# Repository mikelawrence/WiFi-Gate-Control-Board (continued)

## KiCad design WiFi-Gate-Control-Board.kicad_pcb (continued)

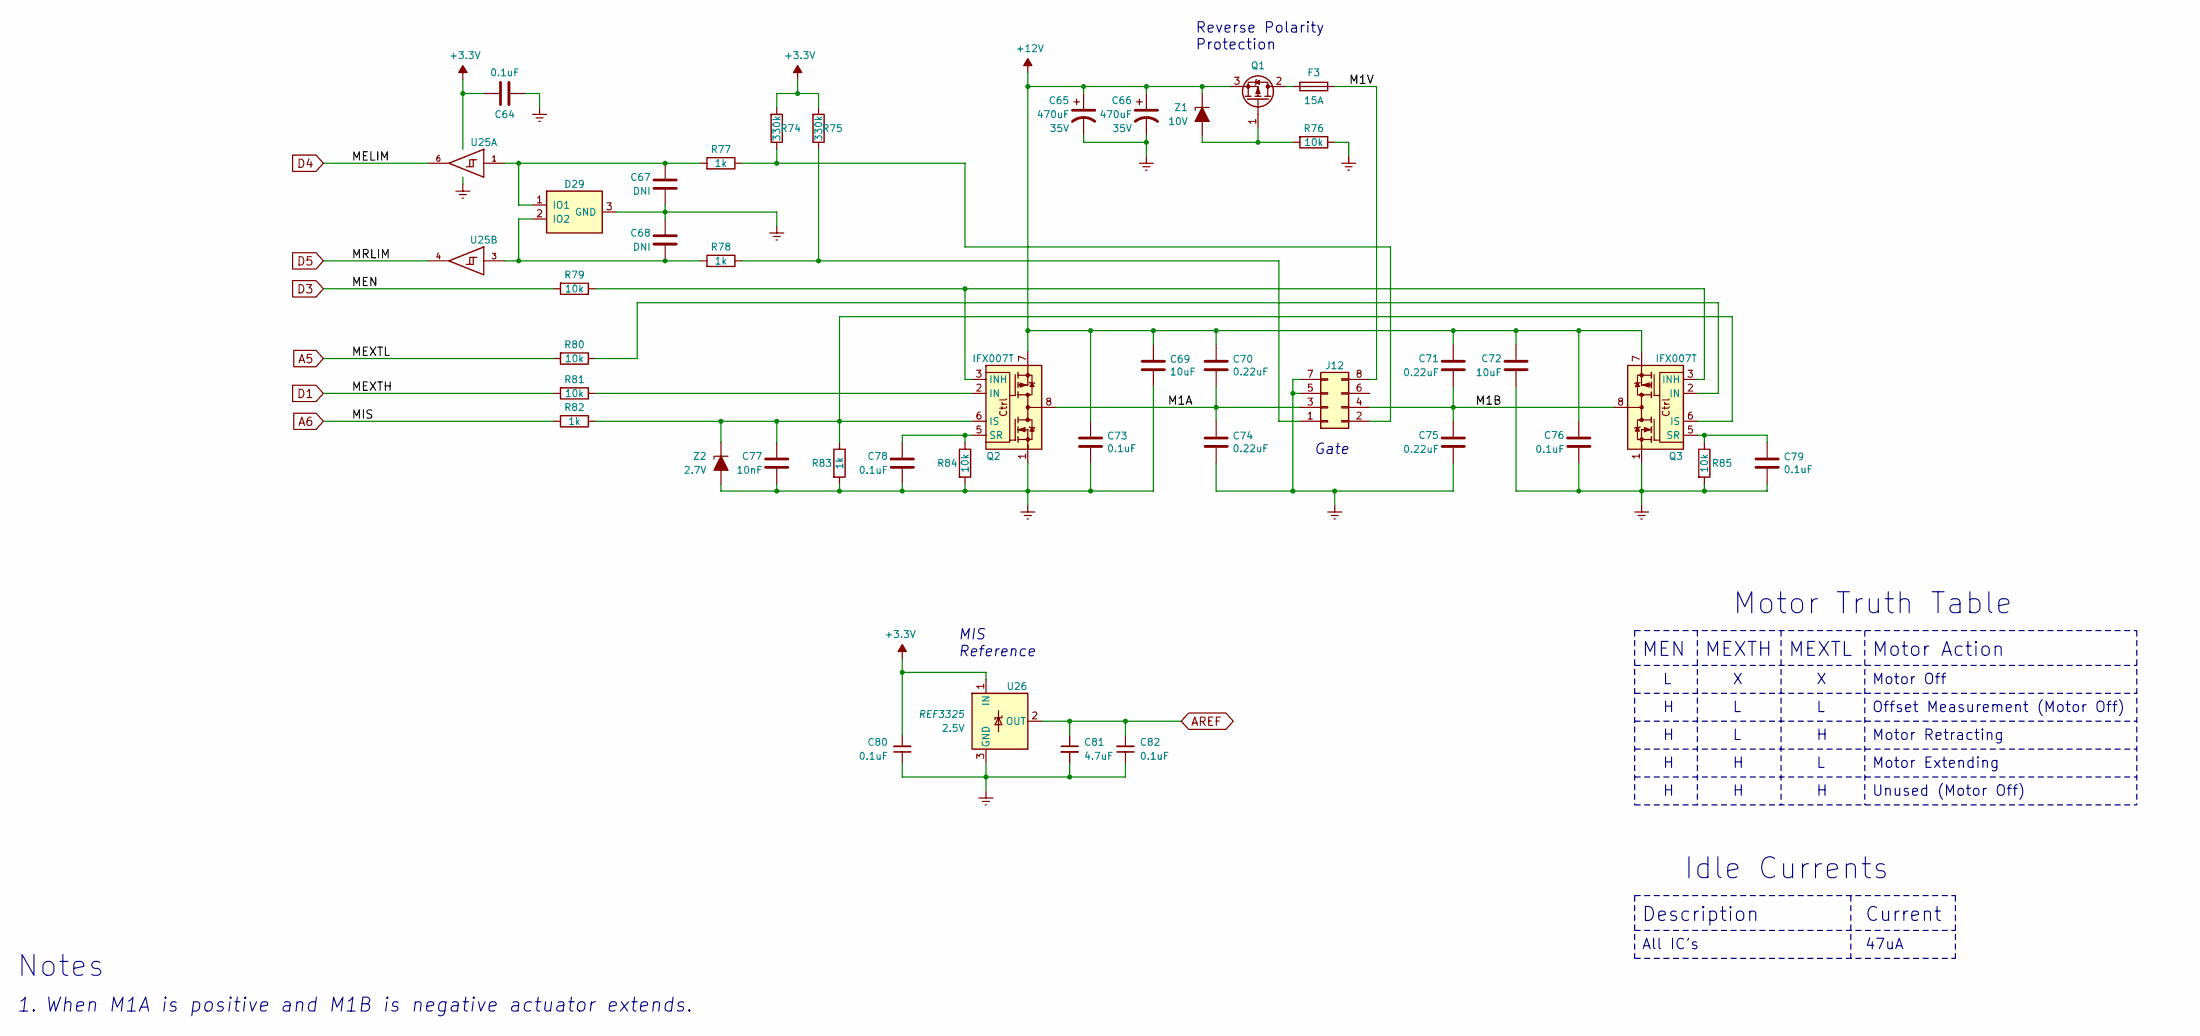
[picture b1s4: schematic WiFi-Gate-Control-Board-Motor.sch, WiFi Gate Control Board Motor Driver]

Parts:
C64, C73, C76, C78, C79, C80, C82: 0.1uF; C_0603_1608Metric; Voltage 50V; Tolerance 5%; Part Number CC603JRX7R9BB104
C65, C66: 470uF; CP_Radial_D16.0mm_P7.50mm; Voltage 35V; Tolerance 20%; Part Number UPM1V471MHD6
C67, C68: DNI; C_0603_1608Metric
C69, C72: 10uF; C_1206_3216Metric; Voltage 50V; Tolerance 10%; Part Number CGA5L1X7R1H106K160AC
C70, C71, C74, C75: 0.22uF; C_0603_1608Metric; Voltage 50V; Tolerance 10%; Part Number UMK107B7224KA-TR
C77: 10nF; C_0603_1608Metric; Voltage 50V; Tolerance 5%; Part Number VJ0603Y103JXACW1BC
C81: 4.7uF; C_0603_1608Metric; Voltage 6.3V; Tolerance 10%; Part Number JMK107BB7475KA-T
D29: TPD2E2U06; SOT-323_SC-70; Part Number TPD2E2U06QDCKRQ1
F3: 15A; Fuseholder_Blade_Mini_Keystone_3568; Part Number 3568
J12: Motor; TE_MATE-N-LOK_350212-1_2X04_P4.95_Vertical; Part Number 350212-1
Q1: IPD90P03P4L-04; TO-252-2; Part Number IPD90P03P4L-04
Q2, Q3: IFX007T; TO-263-7_TabPin8; Part Number IFX007TAUMA1
R74, R75: 330k; R_1206_3216Metric; Tolerance 5%; Part Number ERJ-P08J334V
R76, R79, R80, R81, R84, R85: 10k; R_0603_1608Metric; Tolerance 0.5%; Part Number RR0816P-103-D
R77, R78: 1k; R_1206_3216Metric; Tolerance 0.5%; Part Number AC1206DR-071KL
R82, R83: 1k; R_0603_1608Metric; Tolerance 1%; Part Number ERJ-3EKF1001V
U25: 74LVC2G17; SOT-23-6; Part Number SN74LVC2G17DBVR
U26: REF3325; SOT-23; Voltage 2.5V; Part Number REF3325AIDBZR
Z1: 10V; D_SOT-23_ANK; Part Number SZBZX84C10LT1G
Z2: 2.7V; D_SOT-23_ANK; Part Number SZBZX84C2V7LT1G

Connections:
+3.3V: C64.2, C80.2, R74.2, R75.2, U25.5 (VCC), U26.1 (IN); also elsewhere on the board
+12V: C65.1, C66.1, C69.1, C70.1, C71.1, C72.1, C73.1, C76.1, Q1.3 (S), Q2.7, Q3.7, Z1.1 (K); also elsewhere on the board
/Motor Driver/M1A: C70.2, C74.1, J12.3, Q2.4, Q2.8
/Motor Driver/M1B: C71.2, C75.1, J12.4, Q3.4, Q3.8
/Motor Driver/M1V: F3.1, J12.8
A5: R80.2; also elsewhere on the board
A6: R82.2; also elsewhere on the board
AREF: C81.1, C82.2, U26.2 (OUT); also elsewhere on the board
D1: R81.2; also elsewhere on the board
D3: R79.2; also elsewhere on the board
D4: U25.6; also elsewhere on the board
D5: U25.4; also elsewhere on the board
GND: C64.1, C65.2, C66.2, C67.2, C68.1, C69.2, C72.2, C73.2, C74.2, C75.2, C76.2, C77.2, C78.2, C79.2, C80.1, C81.2, C82.1, D29.3 (GND), J12.5, J12.7, Q2.1, Q3.1, R76.1, R83.2, R84.2, R85.2, U25.2 (GND), U26.3 (GND), Z2.2 (A); also elsewhere on the board
unnamed: C67.1, D29.1 (IO1), R77.2, U25.1
unnamed: C68.2, D29.2 (IO2), R78.2, U25.3
unnamed: C77.1, Q2.6 (IS), Q3.6 (IS), R82.1, R83.1, Z2.1 (K)
unnamed: C78.1, Q2.5 (SR), R84.1
unnamed: C79.1, Q3.5 (SR), R85.1
unnamed: F3.2, Q1.2 (D)
unnamed: J12.1, R75.1, R78.1
unnamed: J12.2, R74.1, R77.1
unnamed: Q1.1 (G), R76.2, Z1.2 (A)
unnamed: Q2.2 (IN), R81.1
unnamed: Q2.3 (INH), Q3.3 (INH), R79.1
unnamed: Q3.2 (IN), R80.1

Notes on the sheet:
Gate
When M1A is positive and M1B is negative actuator extends.
Reverse Polarity Protection
MEXTH
MEN
Motor Action
Motor Off
Motor Extending
Motor Retracting
MIS Reference
All IC’s
Description
Current
47uA
Idle Currents
Notes
MEXTL
Offset Measurement (Motor Off)
Unused (Motor Off)
Motor Truth Table

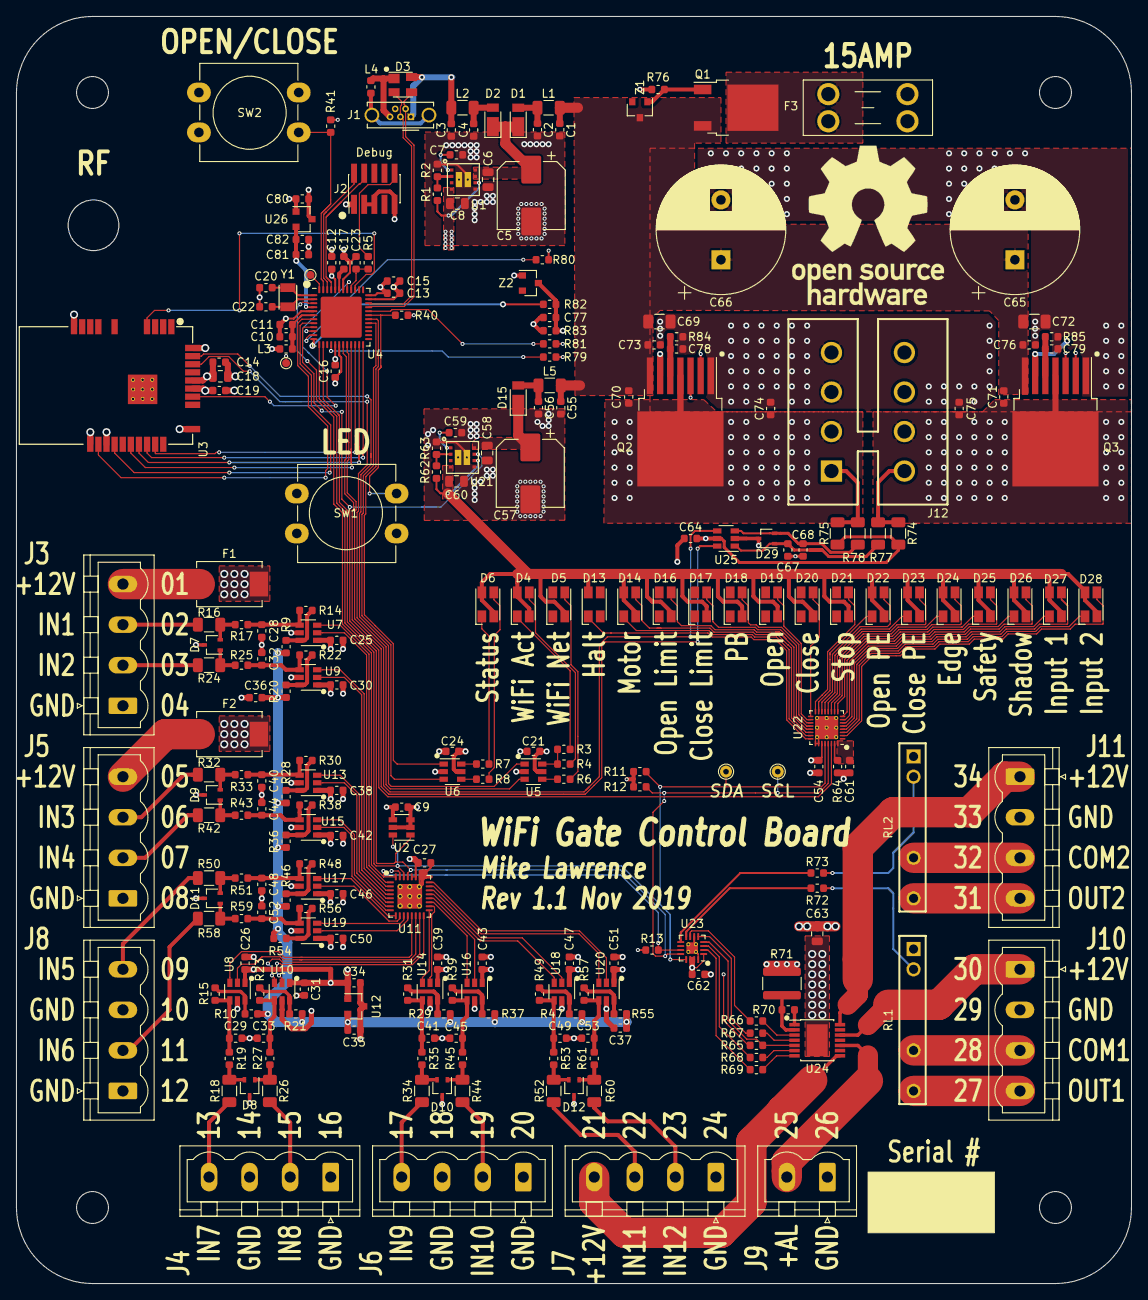
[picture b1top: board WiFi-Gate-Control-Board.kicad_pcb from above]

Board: 4 copper layers, 139.7 x 158.8 mm, 257 parts (0 on the bottom side), 200 nets.

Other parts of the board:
RF: Val**; SMA_Bulkhead_Mount

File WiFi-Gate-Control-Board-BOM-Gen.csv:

Quantity,References,Value,Description,Manufacturer,Part Number,Vendor,Vendor Part Number
6,C1 C2 C3 C4 C55 C56,1nF,"CAP, 0603, 1nF, 10%, X7R, 10V",Vishay,VJ0603Y102KXAAC31,Mouser,77-VJ0603Y102KXAAC31
2,C5 C57,100uF,"CAP, SMD 8X10, 100uF, 20%, EC, 35V",United Chemi-Con,EMVH350ADA101MHA0G,Mouser,661-EMVH350ADA101M
6,C6 C8 C18 C58 C60 C63,22uF,"CAP, 0805, 22uf, 20%, X5R, 25V",Taiyo Yuden,TMK212BBJ226MG-TT,Mouser,963-TMK212BBJ226MGTT
2,C7 C59,3.3nF,"CAP, 0603, 3.3nF, 5%, X7R, 10V",Vishay,VJ0603Y332JXQPW1BC,Mouser,77-VJ0603Y332JXQPBC
33,C9 C11 C12 C13 C14 C16 C21 C23 C24 C25 C26 C27 C30 C31 C34 C36 C37 C38 C39 C42 C43 C46 C47 C50 C51 C62 C64 C73 C76 C78 C79 C80 C82,0.1uF,"CAP, 0603, 0.1uF, 5%, X7R, 50V",Yageo,CC603JRX7R9BB104,Mouser,603-CC603JRX7R9BB104
3,C10 C15 C81,4.7uF,"CAP, 0603, 4.7uf, 10%, X7R, 6.3V",Taiyo Yuden,JMK107BB7475KA-T,Mouser,963-JMK107BB7475KA-T
17,C17 C19 C28 C29 C32 C33 C35 C40 C41 C44 C45 C48 C49 C52 C53 C54 C61,1uF,"CAP, 0603, 1uF, 10%, X5R, 50V",Taiyo Yuden,UMK107BJ105KA-T,Mouser,963-UMK107BJ105KA-T
2,C20 C22,15pF,"CAP, 0603, 15pF, 5%, C0G, 50V",AVX,06035A150JAT2A,Mouser,581-06035A150J
2,C65 C66,470uF,"CAP, THT 16X15, 470uF, 20%, EC, 35V",Nichicon,UPM1V471MHD6,Mouser,647-UPM1V471MHD6
2,C67 C68,DNI,"CAP, 0603, Not Installed",,,,
2,C69 C72,10uF,"CAP, 1206, 10uF, 10%, X7R, 50V",TDK,CGA5L1X7R1H106K160AC,Mouser,810-CGA5L1X7R1H106K1
4,C70 C71 C74 C75,0.22uF,"CAP, 0603, 0.22uF, 10%, X7R, 50V",Taiyo Yuden,UMK107B7224KA-TR,Mouser,963-UMK107B7224KA-TR
1,C77,10nF,"CAP, 0603, 10nF, 5%, X7R, 50V",Vishay,VJ0603Y103JXACW1BC,Mouser,77-VJ0603Y103JXACBC
3,D1 D2 D15,DFLS130,"DIO, PowerDI123, Schottky Rectifier, 30V, 1A",Diodes Inc,DFLS130LQ,Mouser,621-DFLS130L
1,D3,PRTR5V0U2X,"TVS, SOT143, ESD Protection, USB",Nexperia,"PRTR5V0U2X,215",Mouser,771-PRTR5V0U2X-T/R
18,D4 D5 D6 D13 D14 D16 D17 D18 D19 D20 D21 D22 D23 D24 D25 D26 D27 D28,Red/Green,"LED, PLCC4, Red/Green",Avago,HSMF-A203-A00J1,Mouser,630-HSMF-A203-A00J1
7,D7 D8 D9 D10 D11 D12 D29,TPD2E2U06,"TVS, SC70-3, ESD TVS Protection, Dual",Texas Instruments,TPD2E2U06QDCKRQ1,Mouser,595-TPD2E2U06QDCKRQ1
2,F1 F2,0.75A,"Fuse, PTC Resettable, 0.75A, SMT",Bourns,MFSM075-2,Mouser,652-MFSM075-2
1,F3,15A,"Fuse, Mini Fuse Holder",Keystone,3568,Mouser,534-3568
1,J1,USB_B_Micro,"CON, THT, Micro USB 2.0 Type AB, Vertical",Wurth Electronics,614105150721,Mouser,710-614105150621
1,J2,Cortex Debug,"CON, SMD, 1.27mm Header, Dual Row, Vertical, 10 Pos",Samtec,FTSH-105-01-L-DV-K,Mouser,200-FTSH10501LDVK
8,J3 J4 J5 J6 J7 J8 J10 J11,Screw Header 4 Pos,"CON, THT, 5.08mm Pluggable Terminal Header, 4 Pos",Phoenix Contact,1755752,Mouser,651-1755752
8,,Screw Header 4 Pos,"CON, THT, 5.08mm Pluggable Terminal Plug, 4 Pos",Phoenix Contact,1757035,Mouser,651-1757035
1,J9,Screw Header 2 Pos,"CON, THT, 5.08mm Pluggable Terminal Header, 2 Pos",Phoenix Contact,1755736,Mouser,651-1755736
1,,Screw Header 2 Pos,"CON, THT, 5.08mm Pluggable Terminal Plug, 2 Pos",Phoenix Contact,1757019,Mouser,651-1757019
1,J12,Motor,"CON, THT, MATE-N-LOK, Dual Row, 8 Pos",TE Connectivity,350212-1,Mouser,571-3502121
3,L1 L2 L5,1k@100MHz,"BEAD, 1206, 1k@100MHz, 2A",Murata,BLM31KN102SH1L,Mouser,81-BLM31KN102SH1L
2,L3 L4,470@100MHz,"BEAD, 0603, 470R@100MHz, 1A",Murata,BLM18PG471SN1D,Mouser,81-BLM18PG471SN1D
1,Q1,IPD90P03P4L-04,"TRANSISTOR, TO-252-3, P-CH, -90A, -30V",Infineon,IPD90P03P4L-04,Mouser,726-IPD90P03P4L04
2,Q2 Q3,IFX007T,"IC, Motor Driver, Half Bridge, 55A",Infineon,IFX007TAUMA1,Mouser,726-IFX007TAUMA1
2,R1 R62,1.21M,"RES, 0603, 1.21M, 1/10W, 1%, T100",Yageo,RC0603FR-071M21L,Mouser,603-RC0603FR-071M21L
2,R2 R63,383k,"RES, 0603, 383k, 1/10W, 1%, T100",Panasonic,ERJ-3EKF3833V,Mouser,667-ERJ-3EKF3833V
5,R3 R4 R6 R7 R8,44.2R,"RES, 0603, 44.2R, 1/10W, 1%, T100",Panasonic,ERJ-3EKF44R2V,Mouser,667-ERJ-3EKF44R2V
1,R5,39R,"RES, 0603, 39R, 1/10W, 1%, T100",Panasonic,ERJ-3EKF39R0V,Mouser,667-ERJ-3EKF39R0V
12,R9 R10 R20 R21 R28 R29 R36 R37 R46 R47 R54 R55,33.2k,"RES, 0603, 33.2k, 1/16W, 0.5%, T25",Susumu,RR0816P-3322D51C,Mouser,754-RR0816P-3322D51C
3,R11 R12 R13,4.7k,"RES, 0603, 4.7k, 1/10W, 1%, T100",Panasonic,ERJ-3EKF4701V,Mouser,667-ERJ-3EKF4701V
12,R14 R15 R22 R23 R30 R31 R38 R39 R48 R49 R56 R57,6.81k,"RES, 0603, 6.81k, 1/16W, 0.5%, T25",Susumu,RR0816P-6811D81H,Mouser,754-RR0816P-6811D81H
14,R16 R18 R24 R26 R32 R34 R42 R44 R50 R52 R58 R60 R77 R78,1k,"RES, 1206, 1k, 1/4W, 0.5%, T100",Yageo,AC1206DR-071KL,Mouser,AC1206DR-071KL
22,R17 R19 R25 R27 R33 R35 R43 R45 R51 R53 R59 R61 R66 R67 R68 R69 R76 R79 R80 R81 R84 R85,10k,"RES, 0603, 10k, 1/16W, 0.5%, T25",Susumu,RR0816P-103-D,Mouser,754-RR0816P-103D
3,R40 R41 R65,100k,"RES, 0603, 100k, 1/10W, 1%, T100",Panasonic,ERJ-3EKF1003V,Mouser,667-ERJ-3EKF1003V
1,R64,2.94k,"RES, 0603, 2.94k, 1/10W, 1%, T100",Panasonic,ERJ-3EKF2941V,Mouser,667-ERJ-3EKF2941V
1,R70,2.2k,"RES, 0603, 2.2k, 1/10W, 1%, T100",Panasonic,ERJ-3EKF2201V,Mouser,667-ERJ-3EKF2201V
1,R71,150R,"RES, 1218, 150R, 1W, 1%, T100",Vishay / Dale,CRCW1218150RFKEK,Mouser,71-CRCW1218-150-E3
2,R72 R73,422R,"RES, 0603, 422R, 1/10W, 1%, T100",Panasonic,ERJ-3EKF4220V,Mouser,667-ERJ-3EKF4220V
2,R74 R75,330k,"RES, 1206, 330k, 2/3W, 5%, T200",Panasonic,ERJ-P08J334V,Mouser,667-ERJ-P08J334V
2,R82 R83,1k,"RES, 0603, 1k, 1/10W, 1%, T100",Panasonic,ERJ-3EKF1001V,Mouser,667-ERJ-3EKF1001V
2,RL1 RL2,CPC1511Y,"MODULE, THT, SSR, Normally Open, 450mA",IXYS,CPC1511Y,Mouser,849-CPC1511Y
2,SW1 SW2,~,"SW, THT, Push Button",Wurth Electronics,430476085716,Mouser,710-430476085716
2,U1 U21,LMZ21700,"MODULE, SMD, Simple Switcher, 17V, 650mA",Texas Instruments,LMZ21700SILR,Mouser,595-LMZ21700SILR
1,U2,TMP100,"IC, SOT-23-6, I2C Temperature Sensor",Texas Instruments,TMP100AQDBVRQ1,Mouser,595-TMP100AQDBVRQ1
1,U3,ATWINC1500-MR210UB,"MODULE, SMD, WiFi, u.FL connector",Microchip,ATWINC1500-MR210UB1140,Mouser,579-C1500MR210UB1140
1,U4,SAMD21G18-M,"IC, QFN44, MCU, ARM, 256kB Flash, 32kB SRAM, 48MHz",Microchip,ATSAMD21G18A-MUT,Mouser,556-ATSAMD21G18A-MUT
1,U5,74LVC2G07,"IC, SOT-23-6, Dual Buffer with Open-Drain Outputs",Texas Instruments,SN74LVC2G07DBVR,Mouser,595-SN74LVC2G07DBVR
1,U6,74LVC2G06,"IC, SOT-23-6, Dual Inverter with Open-Drain Outputs",Texas Instruments,SN74LVC2G06DBVR,Mouser,595-SN74LVC2G06DBVR
12,U7 U8 U9 U10 U13 U14 U15 U16 U17 U18 U19 U20,TPS3779,"IC, SOT-23-6, Dual Voltage Detector",Texas Instruments,TPS3779BDBVR,Mouser,595-TPS3779BDBVR
1,U11,TCA6424A,"IC, QFN-32, I2C IO Expander",Texas Instruments,TCA6424ARGJR,Mouser,595-TCA6424ARGJR
1,U12,REF3330,"IC, SOT-23, Voltage Reference, 3.0V, 30ppm",Texas Instruments,REF3330AIDBZR,Mouser,595-REF3330AIDBZR
1,U22,LP5024,"IC, QFN-32, 24-Channel, I2C LED Driver",Texas Instruments,LP5024RSMR,Mouser,595-LP5024RSMR
1,U23,TCA6408A,"IC, VQFN-16, I2C IO Expander",Texas Instruments,TCA6408ARGTR,Mouser,595-TCA6408ARGTR
1,U24,ITS4075Q,"IC, PG-TSDSO-14, 4-Channel, High-Side Power Switch",Infineon,ITS4075Q-EP-DXUMA1,Mouser,726-ITS4075QEPDXUMA1
1,U25,74LVC2G17,"IC, SOT-23-6, Dual Schmitt-Trigger Buffer",Texas Instruments,SN74LVC2G17DBVR,Mouser,595-SN74LVC2G17DBVR
1,U26,REF3325,"IC, SOT-23, Voltage Reference, 2.5V, 30ppm",Texas Instruments,REF3325AIDBZR,Mouser,595-REF3325AIDBZR
1,Y1,32.768kHz,"XTL, SMD, 32.768kHz",Abracon,ABS07-32.768KHZ-9-T,Mouser,815-ABS07-32.768K9T
1,Z1,10V,"Zener, 10V, SOT-23",On Semiconductor,SZBZX84C10LT1G,Mouser,863-SZBZX84C10LT1G
1,Z2,2.7V,"Zener, 2.5V, SOT-23",On Semiconductor,SZBZX84C2V7LT1G,Mouser,863-SZBZX84C2V7LT1G

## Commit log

2019-10-20 Initial commit.
    Design still in progress.
2019-10-24 Rev 1.0 Release
    Added input design and calculations. Added BOM. Added Fuse 3D Model.
2019-12-05 No need for zip file in github
2019-12-05 PCB to Rev 1.1
    Fixed missing Reference Designators on top Silkscreen.
    Reset input on TCA6424A and TCA6408A now connected to 3.3V.
    Added series Schottky Diode to LED power supply input.
    Replaced 1000uF main power capacitor with two 470uF capacitors.
    Replaced DS18B20 temperature sensor with TMP100 temperature sensor.
    Increased LED currents to 25mA
2019-12-05 Remove unecessary files
2019-12-08 Changed Cortex Debug connector. Added fabrication pdf.
2019-12-08 Remove old fabriction pdf. Update board image.
2019-12-08 First commit of code.
    Supports Visual Studio Code building. Not fully functional.
2019-12-09 Improve the README and documentation.
2019-12-09 Fix broken link in README
2019-12-27 Added Calibration Mode.
2021-11-08 Update README.md
    https://github.com/mikelawrence/WiFi-Gate-Control-Board
